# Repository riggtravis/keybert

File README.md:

# Keybert
Copyright Travis W Rigg

This source describes Open Hardware and is licensed under the CERN-OHL-P
v2

You may redistribute and modify this documentation and make products
using it under the terms of the CERN-OHL-P v2 (https:/cern.ch/cern-ohl).
This documentation is distributed WITHOUT ANY EXPRESS OR IMPLIED
WARRANTY, INCLUDING OF MERCHANTABILITY, SATISFACTORY QUALITY
AND FITNESS FOR A PARTICULAR PURPOSE. Please see the CERN-OHL-P v2
for applicable conditions

## The keeb!
Keybert is an ortholinear split keyboard that is intended to be as inexpensive
as possible when built by ordering everything from scratch (including ordering
the PCBs from a PCB vendor that does custom orders). Keybert is also very basic.
The idea behind that was to keep things as simple as possible for the target
audience. Someday in the future, there may be a more feature rich version of
Keybert with all of the fancy things that make "endgame" keyboards "endgame."
But for now, you can get the full fat version of Keybert for not all that much
money (in the world of custom mechanical keyboards) and without needing to be a
wizard at soldering.

With all of that in mind, there are also some other decisions that have been
made to make Keybert a better keyboard for this target audience. Specifically,
there are absolutely no components with overlapping footprints like what you'd
see on some of the keyboards that Keybert was inspired by (in particular the
Let's Split by wootapoot).

An overall listing of features reads as follows:

1. A PCB that can also act as a bottom caseplate
2. Reversible PCB for cost savings when ordering boards
3. All diodes set outside of key matrix
4. Pro Micro set outside of key matrix
5. I2C (I still have no idea what this actually wins you, but it costs all of 2
   resisters so why exclude it from the schematic!?)
6. PCB designed with tenting in mind

## The Roadmap
There are some milestones that Keybert needs to acheive, as well as some pie in
the sky type dreams that might never be acheived, but hey, they'd be nice

Milestones:
1. ~~Compile all CERN OSH recommended documents (gerbers and PDFs)~~
2. ~~Simplify PCB using [the aisler PCB design rules](https://aisler.community/t/pcb-design-rules/41)~~
3. Try to increase minimal drill size
4. Design switch plate
5. Perform basic cost estimate
6. Identify and resolve value shortcomings
7. Order all parts
8. Test build difficulty
9. Identify issues with prototype
10. User acceptance testing
11. Acheive inner peace, never to look at the mechanical keyboard community ever
   again, thus finally escaping the endless hamster wheel that is... "endgame"

Unreasonable dreams:
* Make use of all pins on the Elite C
* Alternative version using BlackPill microcontroller
* Alps compatibility
* Kailh Choc version
* 3D printed case CAD models
* A group buy (to bring prices down further than their already low target)
* Regular commercial availability (for even cheaper keyboards)

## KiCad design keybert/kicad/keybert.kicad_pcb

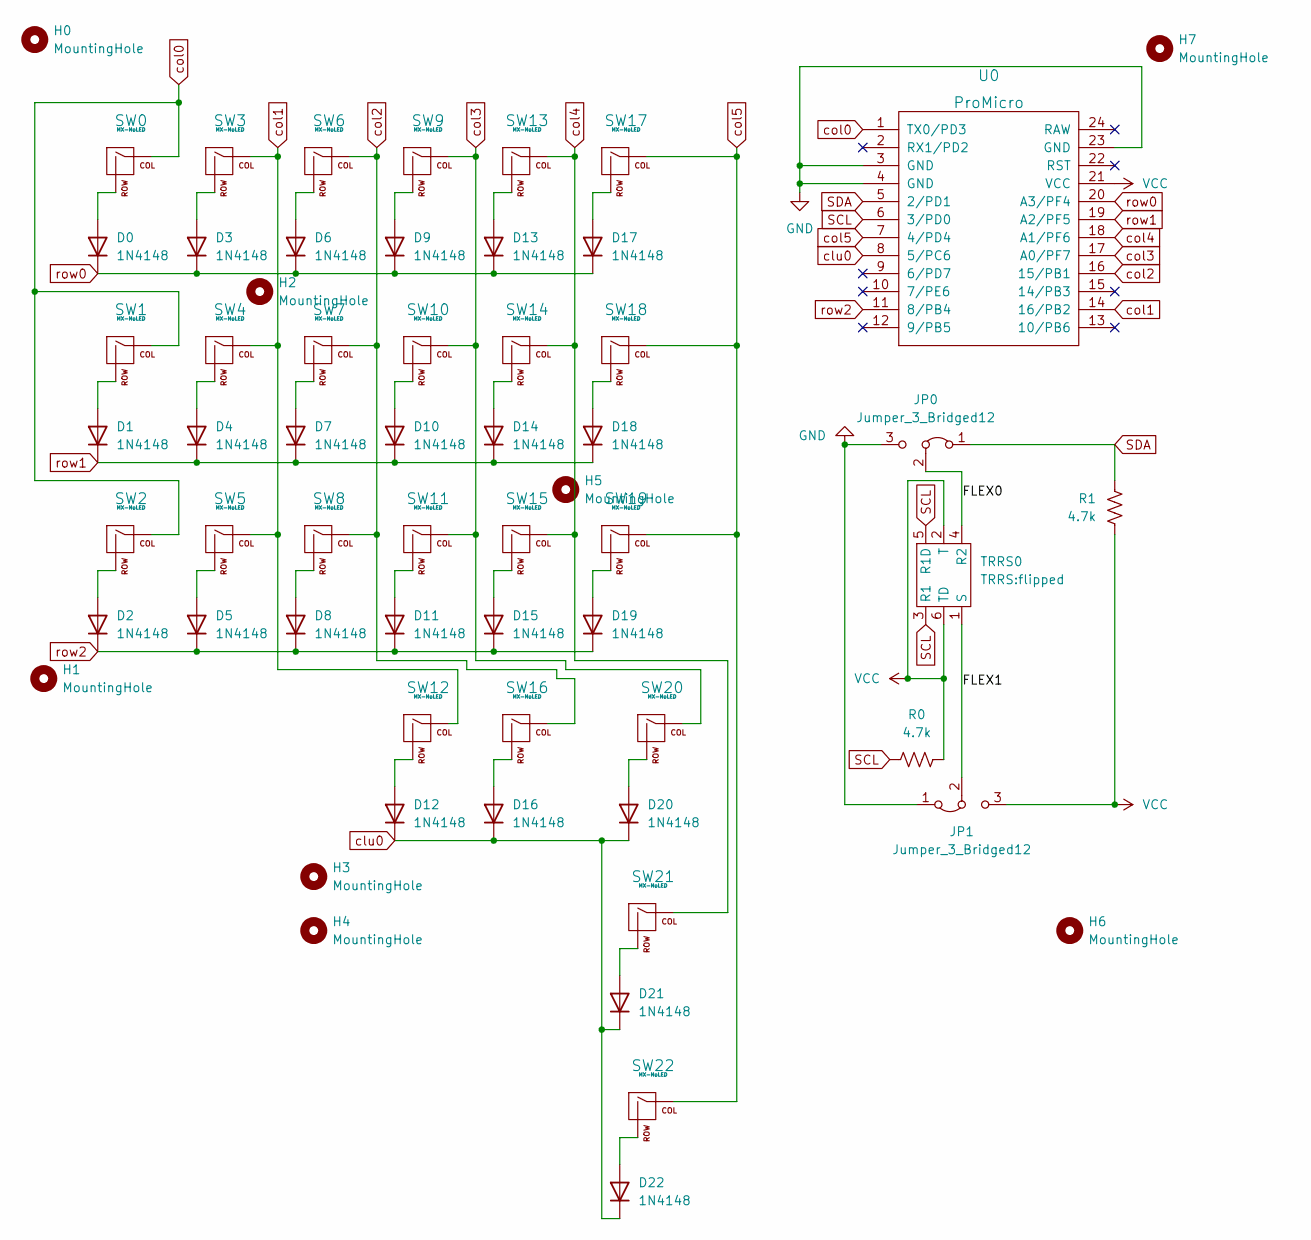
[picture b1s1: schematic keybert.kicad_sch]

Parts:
D0, D1, D2, D3, D4, D5, D6, D7, D8, D9, D10, D11, D12, D13, D14, D15, D16, D17, D18, D19, D20, D21, D22: 1N4148; Diode
H0, H1, H2, H3, H4, H5, H6, H7: MountingHole
JP0, JP1: Jumper_3_Bridged12; PinHeader_1x03_P2.54mm_Vertical
R0, R1: 4.7k; R_Axial_DIN0207_L6.3mm_D2.5mm_P15.24mm_Horizontal
SW0, SW1, SW2, SW3, SW4, SW5, SW6, SW7, SW8, SW9, SW10, SW11, SW12, SW13, SW14, SW15, SW16, SW17, SW18, SW19, SW20, SW21, SW22: MX-NoLED; SW_MX_reversible
TRRS0: TRRS:flipped; TRRS_Jack
U0: ProMicro; ArduinoProMicro

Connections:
/FLEX0: JP0.2 (C), TRRS0.4 (R2)
/FLEX1: JP1.2 (C), TRRS0.1 (S)
GND: JP0.3 (B), JP1.1 (A), U0.3 (GND), U0.4 (GND), U0.23 (GND)
unnamed: D0.2 (A), SW0.2 (ROW)
unnamed: D1.2 (A), SW1.2 (ROW)
unnamed: D2.2 (A), SW2.2 (ROW)
unnamed: D3.2 (A), SW3.2 (ROW)
unnamed: D4.2 (A), SW4.2 (ROW)
unnamed: D5.2 (A), SW5.2 (ROW)
unnamed: D6.2 (A), SW6.2 (ROW)
unnamed: D7.2 (A), SW7.2 (ROW)
unnamed: D8.2 (A), SW8.2 (ROW)
unnamed: D9.2 (A), SW9.2 (ROW)
unnamed: D10.2 (A), SW10.2 (ROW)
unnamed: D11.2 (A), SW11.2 (ROW)
unnamed: D12.2 (A), SW12.2 (ROW)
unnamed: D13.2 (A), SW13.2 (ROW)
unnamed: D14.2 (A), SW14.2 (ROW)
unnamed: D15.2 (A), SW15.2 (ROW)
unnamed: D16.2 (A), SW16.2 (ROW)
unnamed: D17.2 (A), SW17.2 (ROW)
unnamed: D18.2 (A), SW18.2 (ROW)
unnamed: D19.2 (A), SW19.2 (ROW)
unnamed: D20.2 (A), SW20.2 (ROW)
unnamed: D21.2 (A), SW21.2 (ROW)
unnamed: D22.2 (A), SW22.2 (ROW)
SCL: R0.2, TRRS0.3 (R1), TRRS0.5 (R1D), U0.6 (3/PD0)
SDA: JP0.1 (A), R1.1, U0.5 (2/PD1)
VCC: JP1.3 (B), R0.1, R1.2, TRRS0.2 (T), TRRS0.6 (TD), U0.21 (VCC)
clu0: D12.1 (K), D16.1 (K), D20.1 (K), D21.1 (K), D22.1 (K), U0.8 (5/PC6)
col0: SW0.1 (COL), SW1.1 (COL), SW2.1 (COL), U0.1 (TX0/PD3)
col1: SW3.1 (COL), SW4.1 (COL), SW5.1 (COL), SW12.1 (COL), U0.14 (16/PB2)
col2: SW6.1 (COL), SW7.1 (COL), SW8.1 (COL), SW16.1 (COL), U0.16 (15/PB1)
col3: SW9.1 (COL), SW10.1 (COL), SW11.1 (COL), SW20.1 (COL), U0.17 (A0/PF7)
col4: SW13.1 (COL), SW14.1 (COL), SW15.1 (COL), SW21.1 (COL), U0.18 (A1/PF6)
col5: SW17.1 (COL), SW18.1 (COL), SW19.1 (COL), SW22.1 (COL), U0.7 (4/PD4)
row0: D0.1 (K), D3.1 (K), D6.1 (K), D9.1 (K), D13.1 (K), D17.1 (K), U0.20 (A3/PF4)
row1: D1.1 (K), D4.1 (K), D7.1 (K), D10.1 (K), D14.1 (K), D18.1 (K), U0.19 (A2/PF5)
row2: D2.1 (K), D5.1 (K), D8.1 (K), D11.1 (K), D15.1 (K), D19.1 (K), U0.11 (8/PB4)

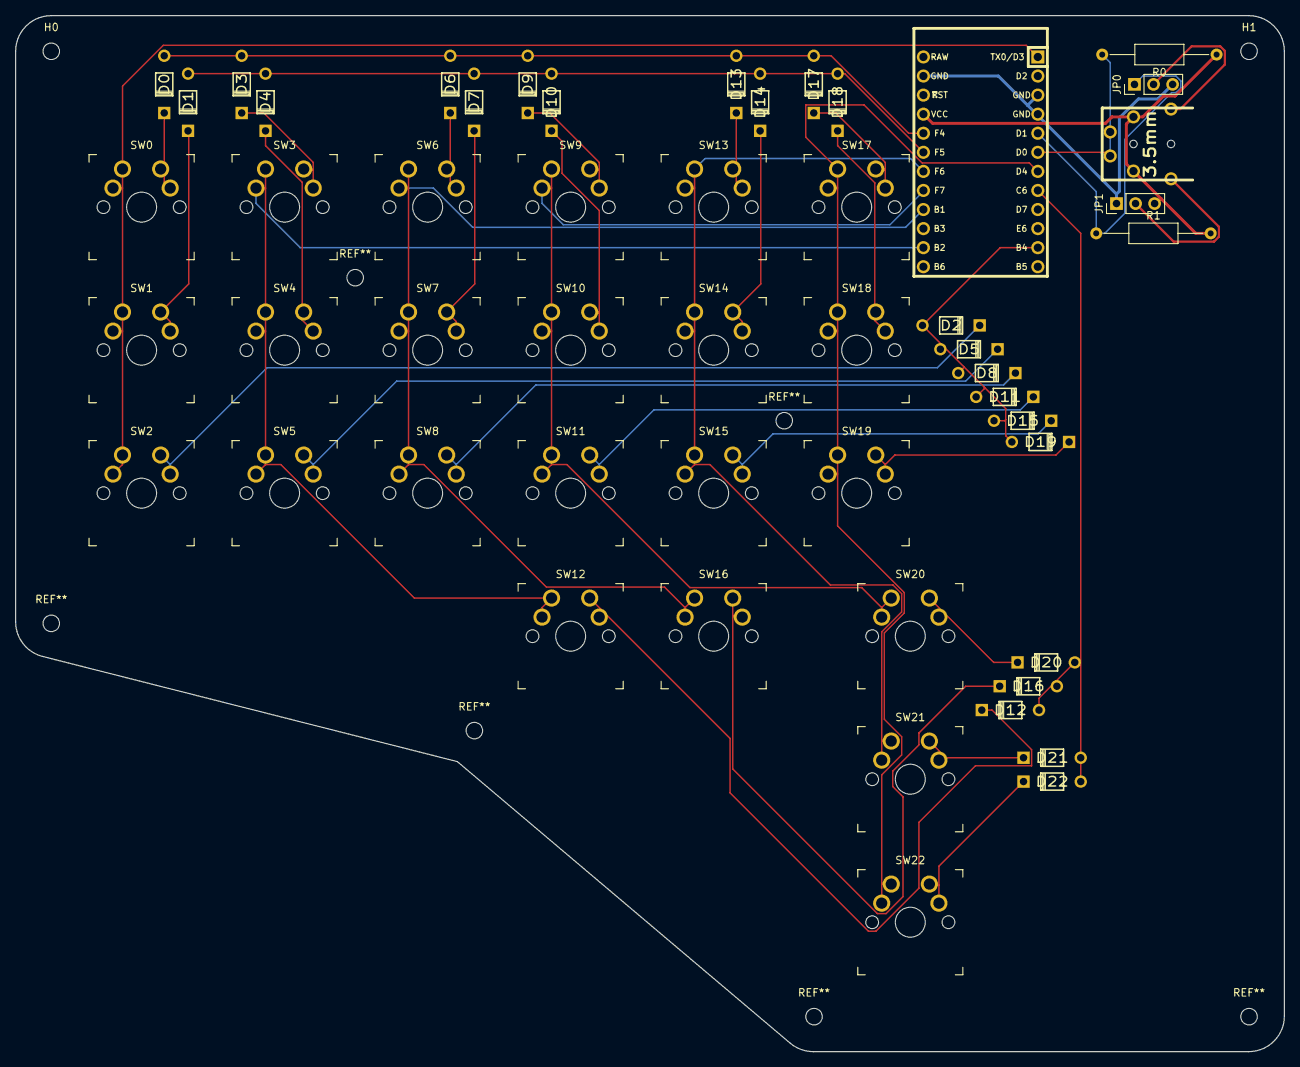
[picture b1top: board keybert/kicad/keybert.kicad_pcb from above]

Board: 2 copper layers, 169.0 x 138.0 mm, 54 parts (1 on the bottom side), 39 nets.

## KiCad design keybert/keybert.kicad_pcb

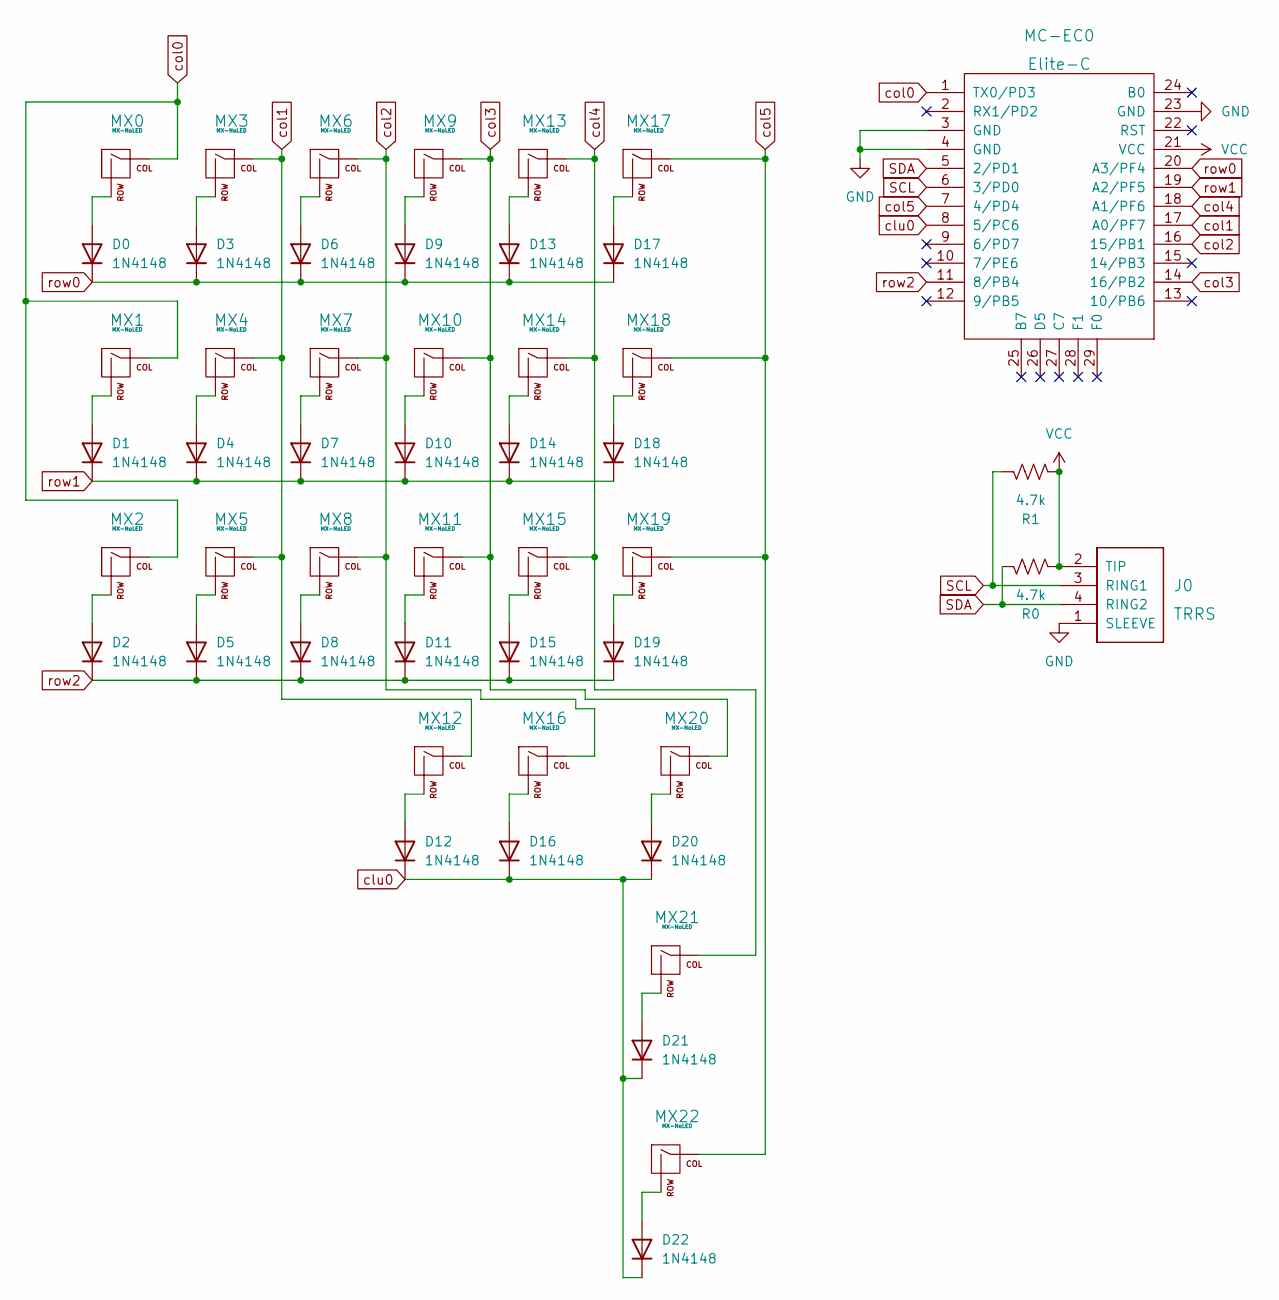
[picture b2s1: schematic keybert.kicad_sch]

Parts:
D0, D1, D2, D3, D4, D5, D6, D7, D8, D9, D10, D11, D12, D13, D14, D15, D16, D17, D18, D19, D20, D21, D22: 1N4148; Diode-dual
J0: TRRS; TRRS-PJ-320A-dual
MC-EC0: Elite-C; Elite-C-castellated-29pin-holes
MX0, MX1, MX2, MX3, MX4, MX5, MX6, MX7, MX8, MX9, MX10, MX11, MX12, MX13, MX14, MX15, MX16, MX17, MX18, MX19, MX20, MX21, MX22: MX-NoLED; SW_MX_reversible
R0, R1: 4.7k; R_Axial_DIN0207_L6.3mm_D2.5mm_P15.24mm_Horizontal

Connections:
GND: J0.1 (SLEEVE), MC-EC0.3 (GND), MC-EC0.4 (GND), MC-EC0.23 (GND)
unnamed: D0.2 (A), MX0.2 (ROW)
unnamed: D1.2 (A), MX1.2 (ROW)
unnamed: D2.2 (A), MX2.2 (ROW)
unnamed: D3.2 (A), MX3.2 (ROW)
unnamed: D4.2 (A), MX4.2 (ROW)
unnamed: D5.2 (A), MX5.2 (ROW)
unnamed: D6.2 (A), MX6.2 (ROW)
unnamed: D7.2 (A), MX7.2 (ROW)
unnamed: D8.2 (A), MX8.2 (ROW)
unnamed: D9.2 (A), MX9.2 (ROW)
unnamed: D10.2 (A), MX10.2 (ROW)
unnamed: D11.2 (A), MX11.2 (ROW)
unnamed: D12.2 (A), MX12.2 (ROW)
unnamed: D13.2 (A), MX13.2 (ROW)
unnamed: D14.2 (A), MX14.2 (ROW)
unnamed: D15.2 (A), MX15.2 (ROW)
unnamed: D16.2 (A), MX16.2 (ROW)
unnamed: D17.2 (A), MX17.2 (ROW)
unnamed: D18.2 (A), MX18.2 (ROW)
unnamed: D19.2 (A), MX19.2 (ROW)
unnamed: D20.2 (A), MX20.2 (ROW)
unnamed: D21.2 (A), MX21.2 (ROW)
unnamed: D22.2 (A), MX22.2 (ROW)
SCL: J0.3 (RING1), MC-EC0.6 (3/PD0), R1.1
SDA: J0.4 (RING2), MC-EC0.5 (2/PD1), R0.1
VCC: J0.2 (TIP), MC-EC0.21 (VCC), R0.2, R1.2
clu0: D12.1 (K), D16.1 (K), D20.1 (K), D21.1 (K), D22.1 (K), MC-EC0.8 (5/PC6)
col0: MC-EC0.1 (TX0/PD3), MX0.1 (COL), MX1.1 (COL), MX2.1 (COL)
col1: MC-EC0.17 (A0/PF7), MX3.1 (COL), MX4.1 (COL), MX5.1 (COL), MX12.1 (COL)
col2: MC-EC0.16 (15/PB1), MX6.1 (COL), MX7.1 (COL), MX8.1 (COL), MX16.1 (COL)
col3: MC-EC0.14 (16/PB2), MX9.1 (COL), MX10.1 (COL), MX11.1 (COL), MX20.1 (COL)
col4: MC-EC0.18 (A1/PF6), MX13.1 (COL), MX14.1 (COL), MX15.1 (COL), MX21.1 (COL)
col5: MC-EC0.7 (4/PD4), MX17.1 (COL), MX18.1 (COL), MX19.1 (COL), MX22.1 (COL)
row0: D0.1 (K), D3.1 (K), D6.1 (K), D9.1 (K), D13.1 (K), D17.1 (K), MC-EC0.20 (A3/PF4)
row1: D1.1 (K), D4.1 (K), D7.1 (K), D10.1 (K), D14.1 (K), D18.1 (K), MC-EC0.19 (A2/PF5)
row2: D2.1 (K), D5.1 (K), D8.1 (K), D11.1 (K), D15.1 (K), D19.1 (K), MC-EC0.11 (8/PB4)

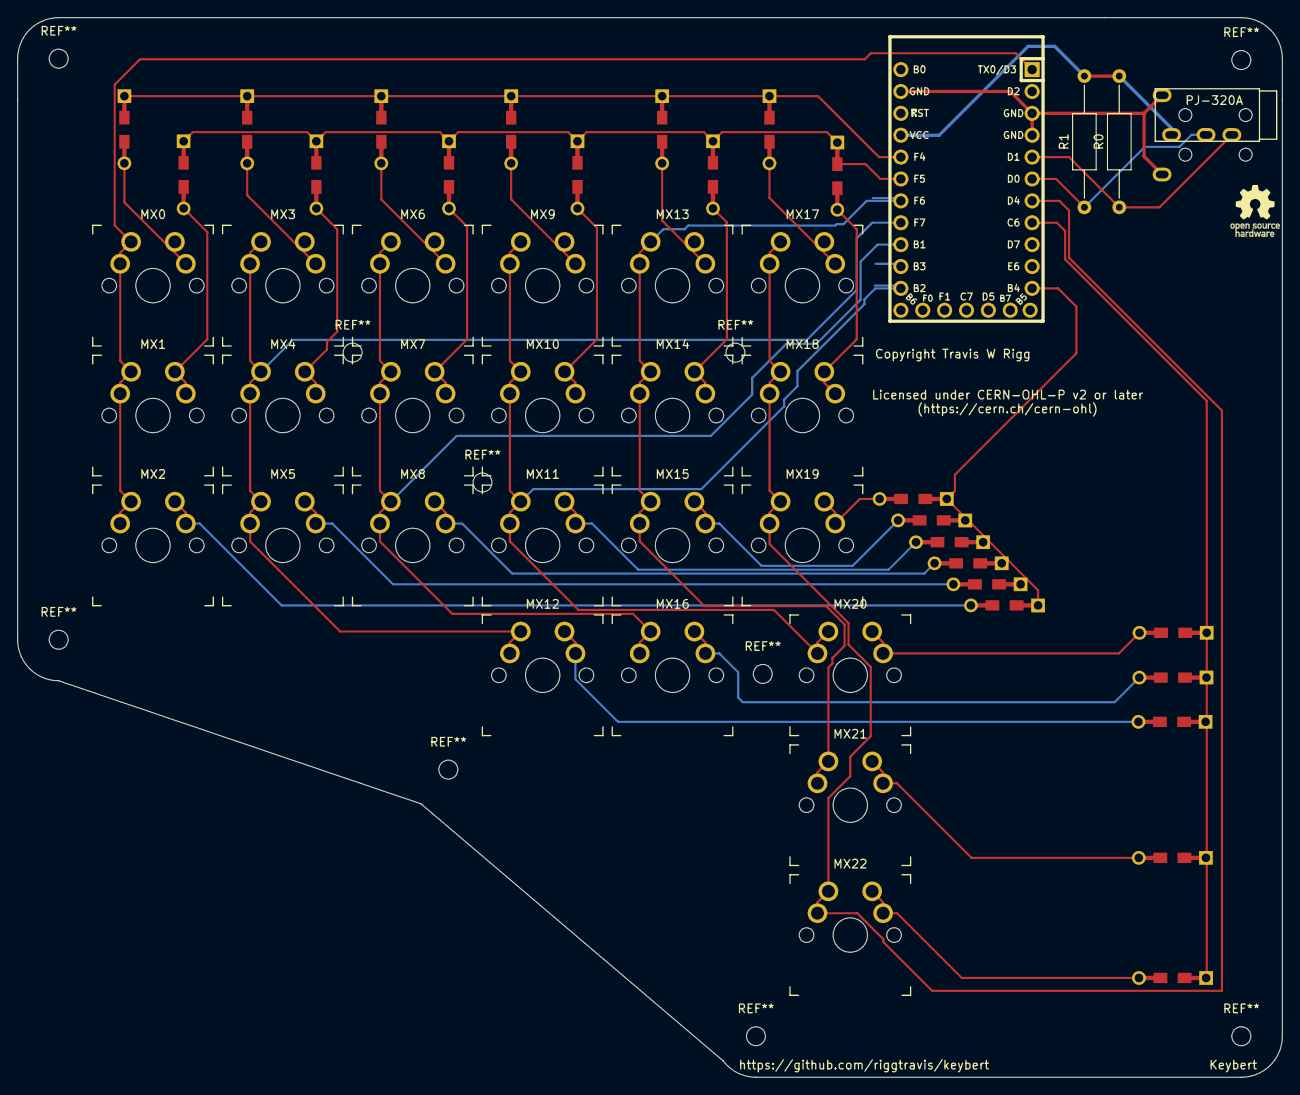
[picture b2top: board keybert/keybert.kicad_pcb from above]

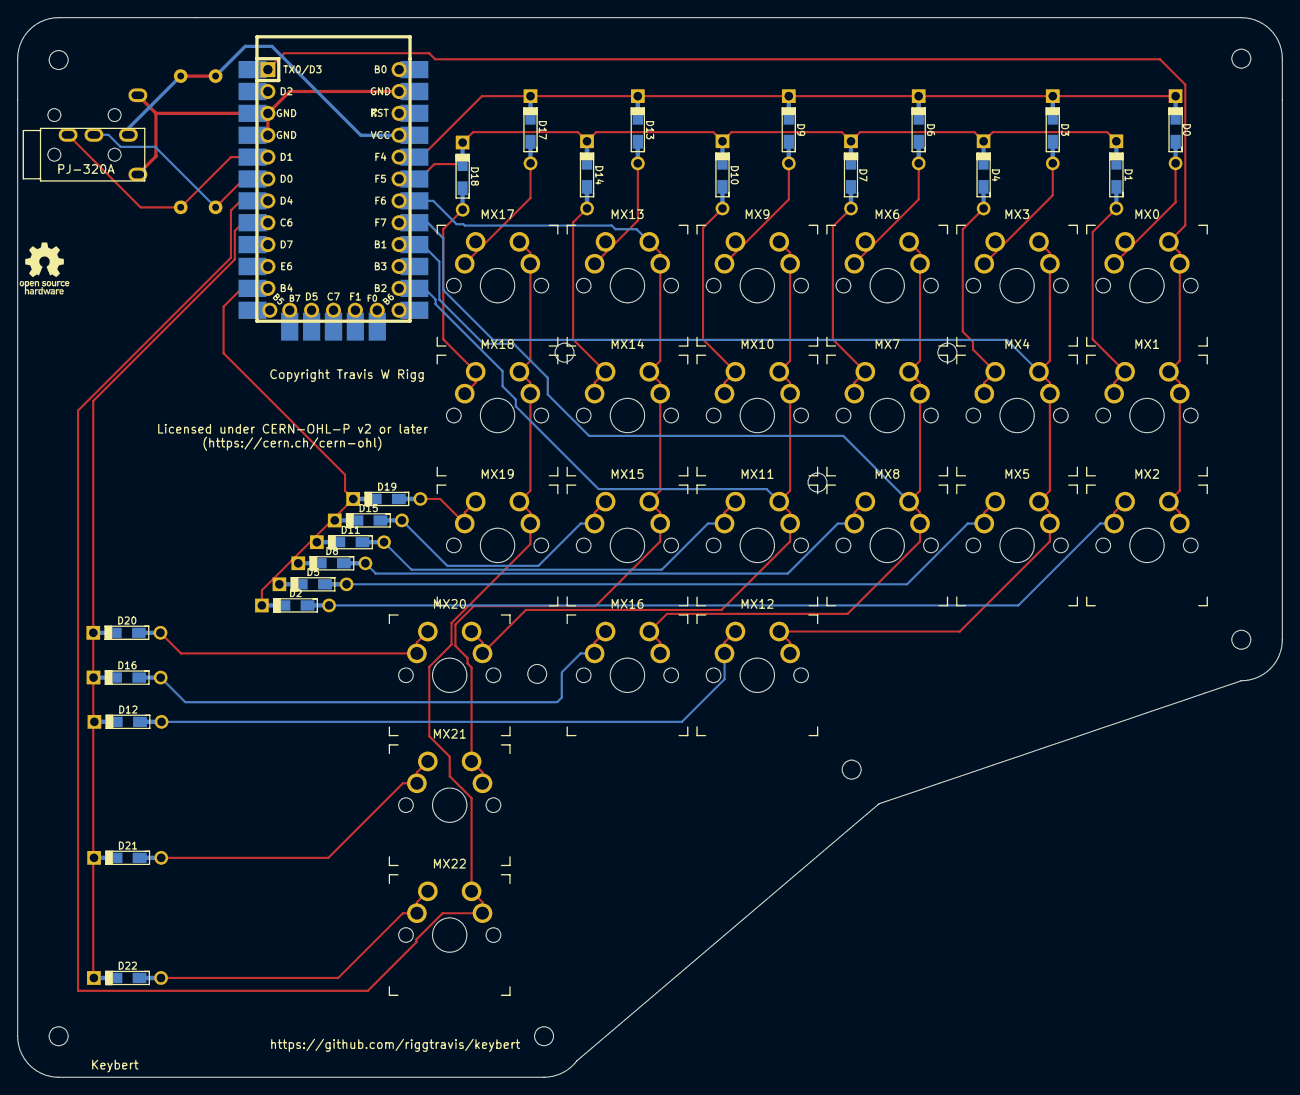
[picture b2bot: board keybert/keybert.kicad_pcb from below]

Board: 2 copper layers, 146.8 x 123.0 mm, 50 parts (24 on the bottom side), 37 nets.

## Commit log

2022-05-16 chore: initialize repo with first iteration of kb
    I have reached a point where I think it's simply time to share this
    keyboard with the world and start making the next steps towards
    building it in physical space. It has everything it needs to at
    least convey the ideas I tried to put into it to make it special
2022-05-17 chore: add yet more to the start of this repo
    Before this is ready to be initially presented to the world, all of
    the licensing should be fully documented and complied with
    fix: typos in the readme
    chore: add more license information, fix warranty
    This should now be reflective of all of the licensing information I
    want included directly within the specification files as well as
2022-05-17 feat: enforced good board geometry using FreeCAD
    Parametric modeling is a wonderful thing and I'm unclear on why
    KiCAD doesn't have it. Oh well, it is what is is. Using the
    dimensions I obtained from the wonderful experience of performing
    my parametric modeling adjustments, I finally had all of the
    information I needed to get pricing for the PCBs as they are
    currently designed. The results were not good. Currently,
2022-05-18 fix: new revision to reduce costs
    Having followed the
    [Aisler design rules](https://aisler.community/t/pcb-design-rules/41)
    I think this new design should be cheaper
2022-05-18 fix: No longer incurring complexity fee
    After a lot of work, the PCB itself should now be viable for ordering.
    At time of completion of that work, the PCB is $30 to be produced in the
    United states in a batch of 3 or $22 to be produced in China in a batch
    of 5. Arguably, that batch of five is more in line with the vision for
    Keybert, however, I would forsee myself preferring the American PCB
    manufacturer for my own boards given overall sociopolitical
2022-05-20 fix: redid PCB due to switch spacing issue
    The spacing of the switches was all wrong I discovered upon loading up
    the switch plate into FreeCAD. I've redone the basic arrangement of all
    electronic parts, but the parts all need, once more to be reconnected.
    I also simplified the schematic slightly. I don't like crossed wires
    even though the ones that do connect are pretty clear thanks to their
    green nodes
2022-05-24 feat: remade parametric model of switch plate
    I'm going to have a friend help me get it sorted out why the parameters
    are coming out so under constrained

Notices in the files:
keybert/keybert.kicad_pcb:
Licensed under CERN-OHL-P v2 or later (https://cern.ch/cern-ohl)
